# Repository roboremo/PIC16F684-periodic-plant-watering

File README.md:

# PIC16F684-periodic-plant-watering
Plant watering system using the PIC16F684 microcontroller.
The MCU commands a 12V solenoid valve to open with specific period, and close after a specific interval.
The period and interval can be configured over Bluetooth using Android phone with RoboRemo app.
The settings are stored in the EEPROM memory of the PIC, so they don't get lost at power OFF.

video: https://www.youtube.com/watch?v=9LrbubgdCc8

Commands:

"get\n" - get parameter values (p = period, i = open interval)  
"time\n" - get up time (how many seconds passed since system was powered)  
"set p [n]\n" - set period, in seconds. Example: "set p 300\n" - valve wil open every 5 minutes  
"set i [n]\n" - set the open interval, in seconds. Example: "set i 20\n" - valve will stay open for 20 seconds  
"open\n" - manually open valve (for test)  
"close\n" - manually close valve (for test)  

The push button is used to turn ON the Bluetooth module, which is off by default, to reduce the power consumption. The system turns off the Bluetooth module automatically after 30s if not receiving any command.

The Bluetooth module used in this project is the BlueSMiRF, configured to 9600 baud.

The blue LED blinks every 2s to signal that system is running.

Current draw (with Bluetooth OFF and valve OFF) is about 6mA.  
That gives a battery life of about 30 days (with 5Ah 12V battery)

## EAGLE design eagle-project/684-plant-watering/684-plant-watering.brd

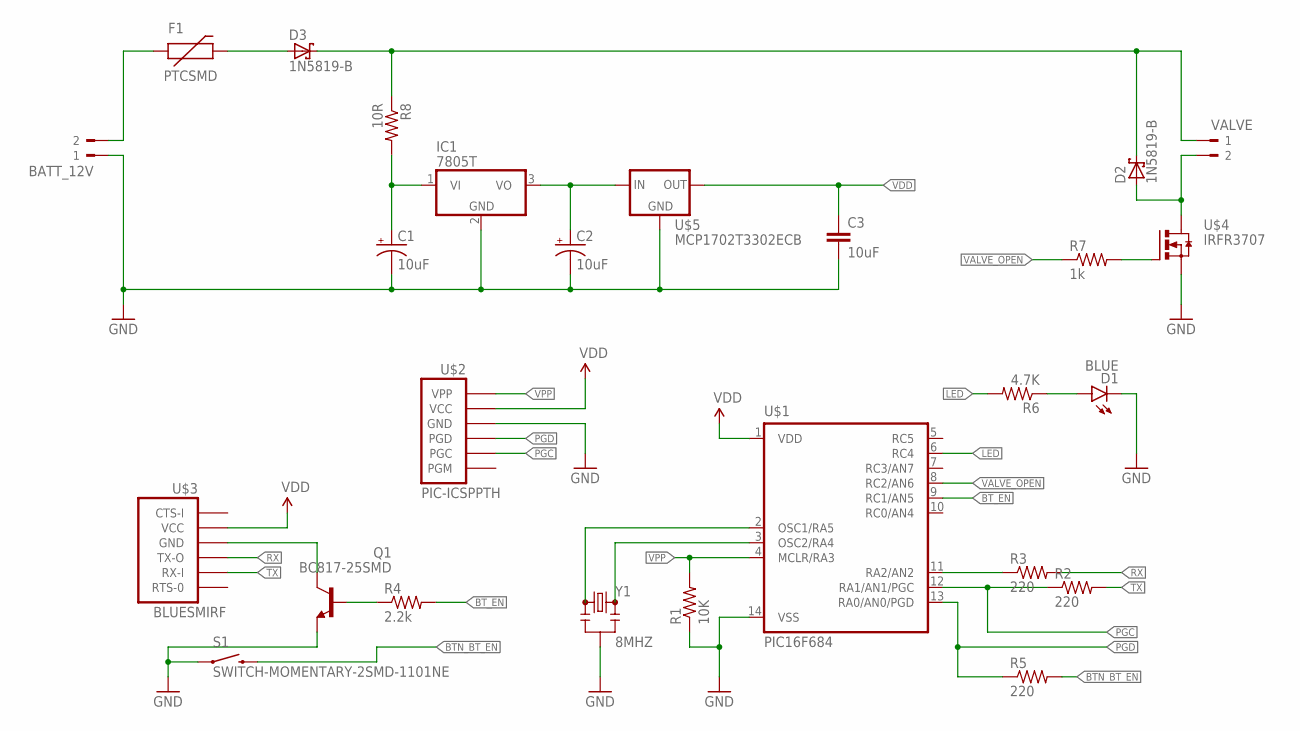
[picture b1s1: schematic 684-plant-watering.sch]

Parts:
BATT_12V: 180-2
C1, C2: 10uF; CPOL-RADIAL-10UF-25V
C3: 10uF; 0603-CAP
D1: BLUE; LED-1206
D2, D3: 1N5819-B; DO41-7.6
F1: PTCSMD; PTC-1206
IC1: 7805T; TO220H
Q1: BC817-25SMD; SOT23-BEC
R1: 10K; 0603-RES
R2, R3, R5: 220; 0603-RES
R4: 2.2k; 0603-RES
R6: 4.7K; 0603-RES
R7: 1k; 0207/10
R8: 10R; 0309/12
S1: SWITCH-MOMENTARY-2SMD-1101NE; TACTILE-SWITCH-1101NE
U$1: PIC16F684; SO14
U$2: PIC-ICSPPTH; MOLEX-1X6
U$3: BLUESMIRF; 1X06
U$4: IRFR3707; TO252
U$5: MCP1702T3302ECB; SOT23
VALVE: 180-2
Y1: 8MHZ; RESONATOR-SMD

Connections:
BTN_BT_EN: R5.2, S1.2
BT_EN: R4.2, U$1.9 (RC1/AN5)
GND: BATT_12V.1, C1.2 (-), C2.2 (-), C3.2, D1.C, IC1.2 (GND), Q1.E, R1.1, S1.1, U$1.14 (VSS), U$2.4 (GND), U$4.3 (S), U$5.1 (GND), Y1.2
LED: R6.2, U$1.6 (RC4)
unnamed: R3.1, U$1.11 (RA2/AN2)
unnamed: Q1.C, U$3.3 (GND)
unnamed: Q1.B, R4.1
unnamed: D1.A, R6.1
unnamed: D2.A, U$4.4 (D), VALVE.2
unnamed: BATT_12V.2, F1.1
unnamed: R7.2, U$4.1 (G)
unnamed: D2.C, D3.C, R8.1, VALVE.1
unnamed: U$1.2 (OSC1/RA5), Y1.1
unnamed: C1.1 (+), IC1.1 (VI), R8.2
unnamed: C2.1 (+), IC1.3 (VO), U$5.3 (IN)
unnamed: U$1.3 (OSC2/RA4), Y1.3
unnamed: D3.A, F1.2
PGC: R2.1, U$1.12 (RA1/AN1/PGC), U$2.2 (PGC)
PGD: R5.1, U$1.13 (RA0/AN0/PGD), U$2.3 (PGD)
RX: R3.2, U$3.4 (TX-O)
TX: R2.2, U$3.5 (RX-I)
VALVE_OPEN: R7.1, U$1.8 (RC2/AN6)
VDD: C3.1, U$1.1 (VDD), U$2.5 (VCC), U$3.2 (VCC), U$5.2 (OUT)
VPP: R1.2, U$1.4 (MCLR/RA3), U$2.6 (VPP)

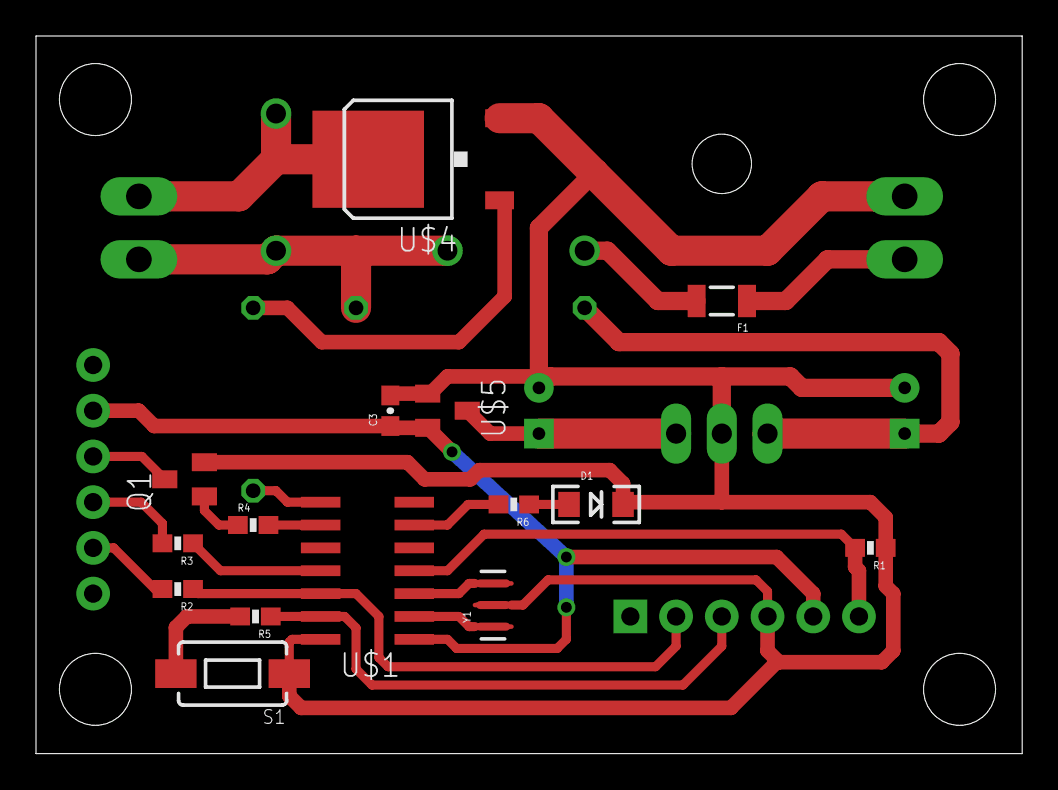
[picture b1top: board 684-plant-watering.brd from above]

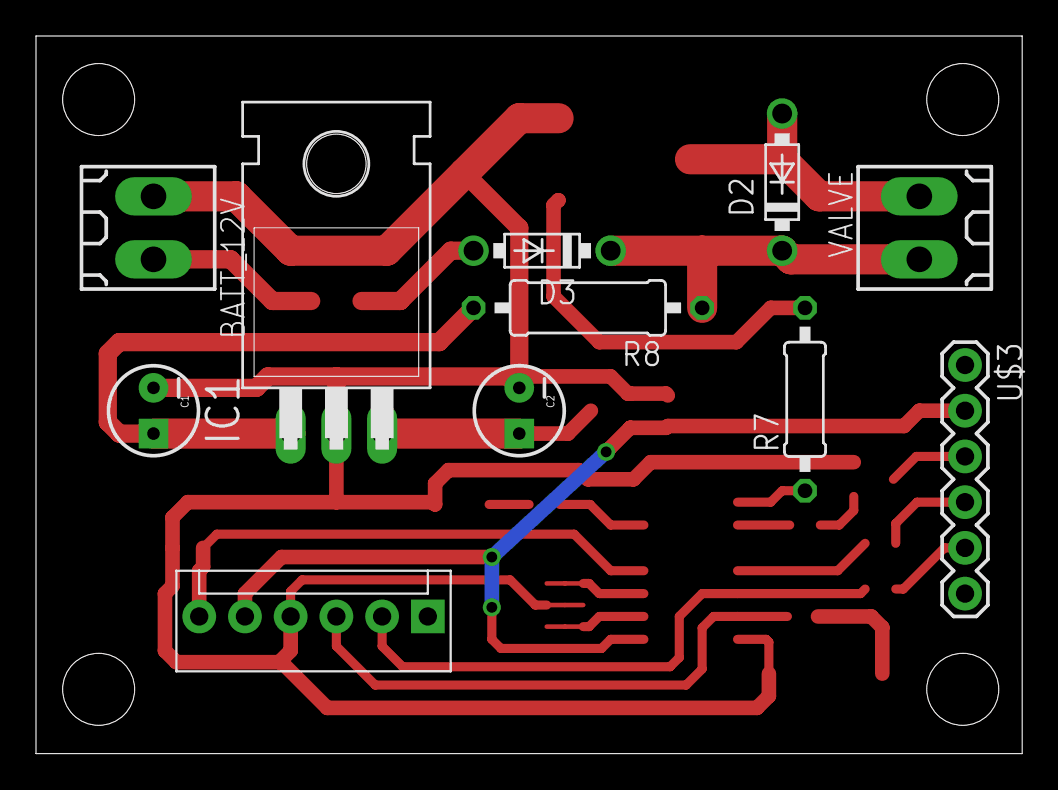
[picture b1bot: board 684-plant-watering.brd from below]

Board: 2 copper layers, 54.8 x 39.9 mm, 26 parts (11 on the bottom side), 24 nets.

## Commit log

2016-08-10 added MPLABX project
2016-08-10 added schematic image and Eagle project
2016-08-23 added RoboRemo interface file
2016-08-23 added link to YouTube video
2016-10-29 Update LICENSE

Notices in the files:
parts and their libraries:
SparkFun-Capacitors: Licensing: Creative Commons ShareAlike 4.0 International - https://creativecommons.org/licenses/by-sa/4.0
